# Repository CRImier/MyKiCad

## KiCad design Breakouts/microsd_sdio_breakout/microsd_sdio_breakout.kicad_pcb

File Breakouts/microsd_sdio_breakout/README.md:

# MicroSD SDIO breakout 

A MicroSD SDIO breakout with data-to-VCC pullups, card detect and decoupling capacitor.
Inspired by [a long-sold-out Tindie listing](https://www.tindie.com/products/gtalusan/microsdtf-breakout-with-pull-up-resistors/)

If you need to disable the CD pullup, you can use a hot air gun and shift the bottom resistor pack up by one resistor.
Pin headers are arranged in a way that this board can be plugged into a breadboard.
Signal names are silkscreened on the board's bottom layer, which is flat - all the components are on the bottom of the board for PnP optimization.
There's a 0805 footprint between card shield and card GND.

- PCB size: 23,5*23,5mm
- Layer count: 2

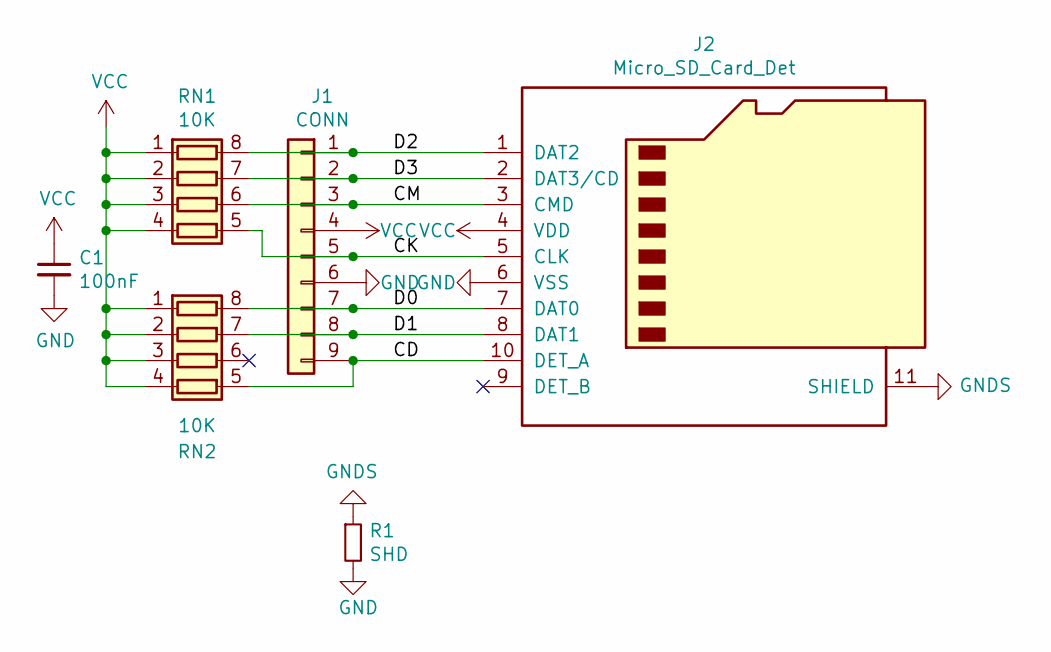
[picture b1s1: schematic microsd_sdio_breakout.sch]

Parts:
C1: 100nF; C_0805_2012Metric
J1: CONN; PinHeader_1x09_P2.54mm_Vertical
J2: Micro_SD_Card_Det; microSD-Receptacle-SelfEject
R1: SHD; R_0805_2012Metric
RN1, RN2: 10K; R_Array_Convex_4x0603

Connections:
/CD: J1.9, J2.10 (DET_A), RN2.5 (R4.2)
/CK: J1.5, J2.5 (CLK), RN1.5 (R4.2)
/CM: J1.3, J2.3 (CMD), RN1.6 (R3.2)
/D0: J1.7, J2.7 (DAT0), RN2.8 (R1.2)
/D1: J1.8, J2.8 (DAT1), RN2.7 (R2.2)
/D2: J1.1, J2.1 (DAT2), RN1.8 (R1.2)
/D3: J1.2, J2.2 (DAT3/CD), RN1.7 (R2.2)
GND: C1.2, J1.6, J2.6 (VSS), R1.2
GNDS: J2.11 (SHIELD), R1.1
VCC: C1.1, J1.4, J2.4 (VDD), RN1.1 (R1.1), RN1.2 (R2.1), RN1.3 (R3.1), RN1.4 (R4.1), RN2.1 (R1.1), RN2.2 (R2.1), RN2.3 (R3.1), RN2.4 (R4.1)

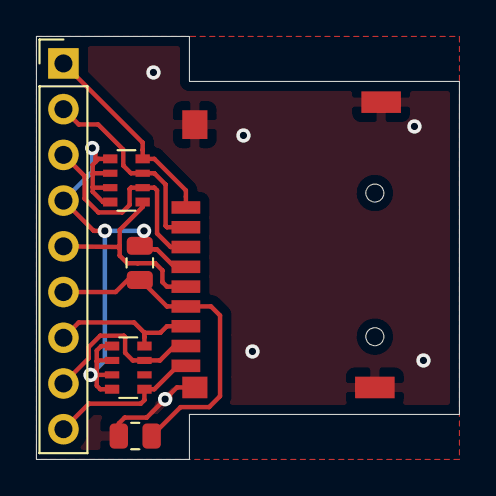
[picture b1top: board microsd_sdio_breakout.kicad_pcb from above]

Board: 2 copper layers, 23.5 x 23.5 mm, 6 parts (0 on the bottom side), 10 nets.

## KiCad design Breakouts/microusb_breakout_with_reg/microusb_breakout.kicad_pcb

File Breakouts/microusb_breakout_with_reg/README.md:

# Simple MicroUSB breakout

This is a MicroUSB connector breakout that also includes a 3.3V regulator. The 5V pin is available on the pin header,
and 3.3V is available on the bottom of the board. Pins are not marked on the bottom of the board.

- PCB size: 8mm*11mm
- Layer count: 2

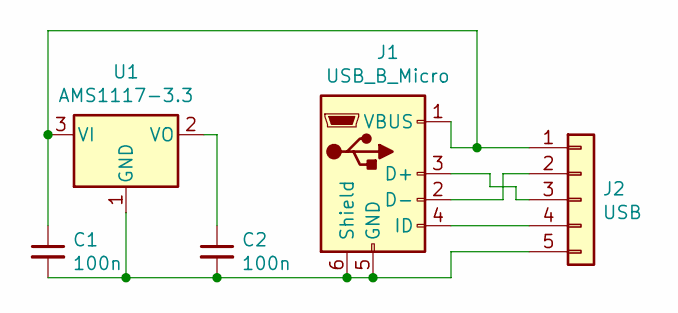
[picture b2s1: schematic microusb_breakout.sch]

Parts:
C1, C2: 100n; C_0805_2012Metric
J1: USB_B_Micro; MICROUSB_REINFORCED
J2: USB; PinHeader_1x05_P2.00mm_Vertical
U1: AMS1117-3.3; SOT-223-3_TabPin2

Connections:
unnamed: C1.1, J1.1 (VBUS), J2.1, U1.3 (VI)
unnamed: C1.2, C2.2, J1.5 (GND), J1.6 (Shield), J2.5, U1.1 (GND)
unnamed: C2.1, U1.2 (VO)
unnamed: J1.2 (D-), J2.2
unnamed: J1.3 (D+), J2.3
unnamed: J1.4 (ID), J2.4

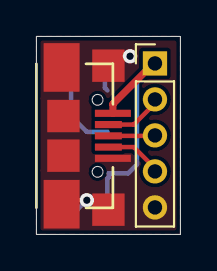
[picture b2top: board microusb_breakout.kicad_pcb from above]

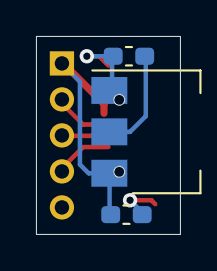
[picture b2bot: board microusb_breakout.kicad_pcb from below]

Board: 2 copper layers, 8.0 x 11.0 mm, 5 parts (3 on the bottom side), 6 nets.

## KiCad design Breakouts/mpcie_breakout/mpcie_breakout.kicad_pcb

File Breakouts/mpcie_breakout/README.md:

# mPCI-E breakout board

This is a mPCI-e (miniPCI-express) receptacle breakout that aims to be as fully-featured as possible while keeping the price low.
It allows you to work with a wide range of mPCIe devices - from consumer-oriented mPCIe cards
(i.e. WiFi, BT, GSM and GPS mPCI-e cards and mSATA drives)
to other cards for hobbyist and specialist use
(mPCI-E breakouts for MCUs, RF-oriented mPCI-E cards and other mPCIe cards of all kinds)

This board has a MicroUSB socket and a SIM socket, as well as a footprint to add 1117-SOT223 compatible linear regulators
from VBUS to 3.3V and 1.5V power lines. All 1.5V pins can be disconnected from the 1.5V power bus in case your card uses these
pins for some other purpose

Keep in mind that PCI-E signals aren't impedance-matched to the PCB, in fact,
the trace thickness and clearances for the diffpairs was not chosen with any specific purpose in mind.

The board is intended to be self-documenting - the signal numbers are silkscreened on the board,
and the PCI-E pinout is written on the bottom of the board. There's also a mSATA pin mapping cheatsheet.

## Changes in v3:

- Moved to Kicad 5
- PCIe diffpairs made a tad better

## Changes in v2:

- SIM slot pinout has been fixed
- Added 1117 footprint regulators for 3.3V and 1.5V lines
- Made standoff holes more compatible with popular solderable standoffs
- Made mounting holes M3 and M4 instead of random diameters, spaced them apart in a way that made more sense
- Changed 0R resistors to 0603 - allowing easier handsoldering of the bottom side (bottom side has optional components for 1.5V and 3.3V regulators)
- Made mPCIe socket alignment pin holes smaller so that they can actually help with alignment
- Made a cutout for USB socket "lips" to allow for easier panelization
- Added fiducials
- Replaced the capacitor footprint with the one used in stock libraries

- Signal names are silkscreened on the board, top and bottom layers.
- This repository also includes files for manufacturing a 3x2 panel.
- I recommend a stencil for assembling this board.

- Software: Kicad 6
- Version: 3
- PCB size: 73*42mm
- Layer count: 2
- Recommended thickness: non-thin

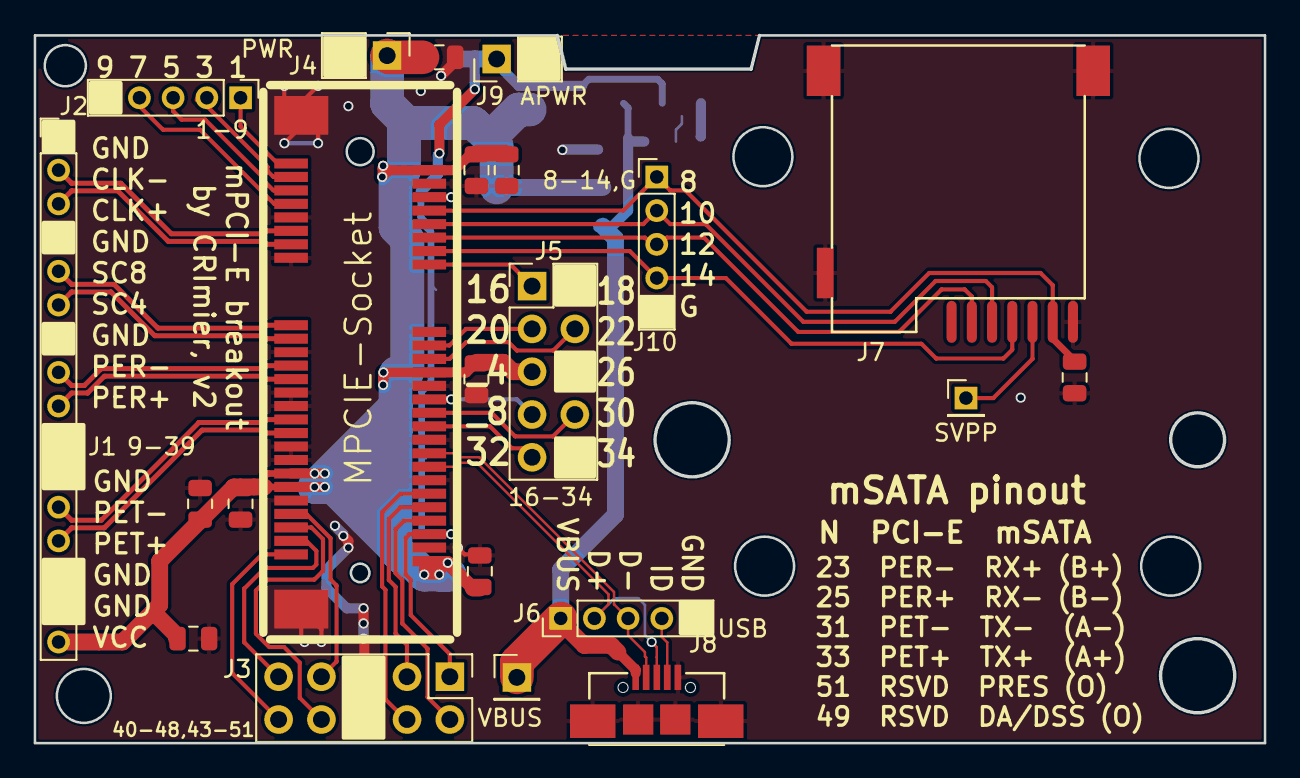
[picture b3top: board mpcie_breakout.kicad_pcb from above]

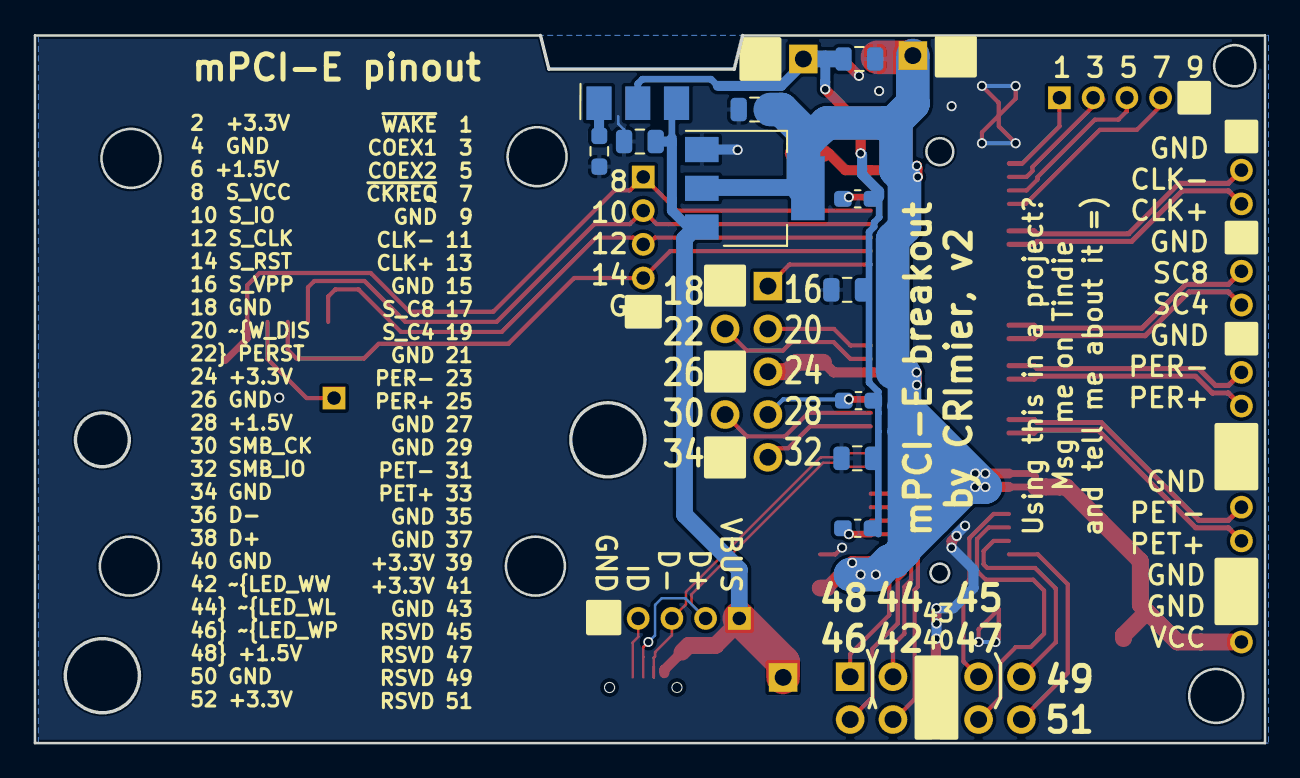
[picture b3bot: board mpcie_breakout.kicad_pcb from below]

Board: 2 copper layers, 73.0 x 42.0 mm, 33 parts (11 on the bottom side), 40 nets.

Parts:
C1, C2, C3, C4, C5, C6, C7, C8, C9, C10, C11, C12, C13, C14: 100nF; C_0805_2012Metric
J1: 9-39; Pin_Header_Straight_1x16_Pitch2.00mm
J2: 1-9; Pin_Header_Straight_1x05_Pitch2.00mm
J3: 40-48,43-51; Pin_Header_Straight_2x05_Pitch2.54mm
J4: PWR; Pin_Header_Straight_1x02_Pitch2.54mm
J5: 16-34; Pin_Header_Straight_2x05_Pitch2.54mm
J6: USB; Pin_Header_Straight_1x05_Pitch2.00mm
J7: SIM_Card; MICROSIM_6P_SMD_HOLDER
J8: USB_OTG; MICROUSB_SIMPLE
J9: APWR; Pin_Header_Straight_1x02_Pitch2.54mm
J10: 8-14,G; Pin_Header_Straight_1x05_Pitch2.00mm
R1, R2, R3: 0; R_0603_1608Metric_Pad1.05x0.95mm_HandSolder
R4: 0/ADJ; R_0603_1608Metric_Pad0.98x0.95mm_HandSolder
TP1: SVPP; Pin_Header_Straight_1x01_Pitch2.00mm
TP2: VBUS; Pin_Header_Straight_1x01_Pitch2.54mm
U1: MPCIE-Socket; mpcie-socket
U2: AP1117-33; SOT-223-3_TabPin2
U3: AP1117-15; SOT-223-3_TabPin2

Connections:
+1V5: C10.1, C11.1, C12.1, J9.1, R1.2, R2.2, R3.2, U3.2
/CLK+: J1.3, U1.13
/CLK-: J1.2, U1.11
/D+: J6.2, J8.3, U1.38
/D-: J6.3, J8.2, U1.36
/PER+: J1.9, U1.25
/PER-: J1.8, U1.23
/PET0+: J1.13, U1.33
/PET0-: J1.12, U1.31
/SIM_CLK: J7.C3, J10.3, U1.12
/SIM_IO: J7.C7, J10.2, U1.10
/SIM_RST: J7.C2, J10.4, U1.14
/SIM_VCC: C9.1, J7.C1, J10.1, U1.8
/SIM_VPP: J7.C6, TP1.1
/SMH+: J1.6, U1.19
/SMH-: J1.5, U1.17
GND: C1.2, C2.2, C3.2, C4.2, C5.2, C6.2, C7.2, C8.2, C9.2, C10.2, C11.2, C12.2, C13.2, C14.2, J1.1, J1.4, J1.7, J1.10, J1.11, J1.14, J1.15, J2.5, J3.5, J3.6, J4.2, J5.2, J5.6, J5.10, J6.5, J7.8, J7.C5, J8.5, J8.6, J9.2, J10.5, R4.2, U1.4, U1.9, U1.15, U1.18, U1.21, U1.26, U1.27, U1.29, U1.34, U1.35, U1.37, U1.40, U1.43, U1.50, U2.1
unnamed: J2.1, U1.1
unnamed: J2.2, U1.3
unnamed: J2.3, U1.5
unnamed: J2.4, U1.7
unnamed: J3.1, R3.1, U1.48
unnamed: J3.2, U1.46
unnamed: J3.3, U1.44
unnamed: J3.4, U1.42
unnamed: J3.7, U1.45
unnamed: J3.8, U1.47
unnamed: J3.9, U1.49
unnamed: J3.10, U1.51
unnamed: J5.1, U1.16
unnamed: J5.3, U1.20
unnamed: J5.4, U1.22
unnamed: J5.7, R2.1, U1.28
unnamed: J5.8, U1.30
unnamed: J5.9, U1.32
unnamed: J6.4, J8.4
unnamed: R1.1, U1.6
unnamed: R4.1, U3.1
VBUS: C14.1, J6.1, J8.1, TP2.1, U2.3, U3.3
VCC: C1.1, C2.1, C3.1, C4.1, C5.1, C6.1, C7.1, C8.1, C13.1, J1.16, J4.1, J5.5, U1.2, U1.24, U1.39, U1.41, U1.52, U2.2

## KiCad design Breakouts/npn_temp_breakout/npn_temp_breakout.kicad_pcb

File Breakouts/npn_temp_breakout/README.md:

# PNP transistor temperature sensing breakout

This is a board I plan to use with MAX6636 for temperature sensing. It's a PNP (3906)
transistor breakout with two of the transistor's legs joined together. The MAX6636 datasheet
is weird in that it calls for a 3904 transistor in its recommended parts section, which is NPN,
but the schematic symbols and the datasheet mentions PNP transistors. I didn't check if this
breakout would be suitable for 3904, this is all yet to be tested properly.

The pad with silkscreen square around it is the "+" pad for PNP transistor, if I'm not mistaken.

There's a copper via going from the bottom layer to the top layer, to where the transistor is:
my intention is that it ought to make thermal transfer better. I'm not sure if this is actually
the case. Oh, also, there's an exposed copper polygon on the bottom, but it'll break if you
reload the netlist by i.e. F8, so you'll need to re-add a trace from PNP's pin 3 to re-fill it.
Delete the trace after re-filling so that it doesn't cause interference.

I'd recommend connecting these boards to a main board with something like a twisted pair (from i.e. an
Ethernet cable)

This board is untested and there's no guarantees of fitness.

- PCB size: 5.6x4mm
- Layer count: 2

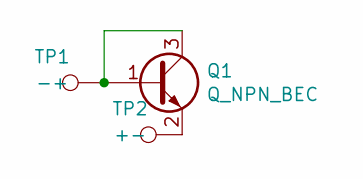
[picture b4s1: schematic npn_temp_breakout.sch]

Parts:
Q1: Q_NPN_BEC; SOT-23
TP1: -+; TestPoint_Pad_1.5x1.5mm
TP2: +-; TestPoint_Pad_1.5x1.5mm

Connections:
unnamed: Q1.1 (B), Q1.3 (C), TP1.1
unnamed: Q1.2 (E), TP2.1

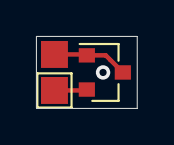
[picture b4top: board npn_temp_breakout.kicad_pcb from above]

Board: 2 copper layers, 5.6 x 4.0 mm, 3 parts (0 on the bottom side), 2 nets.

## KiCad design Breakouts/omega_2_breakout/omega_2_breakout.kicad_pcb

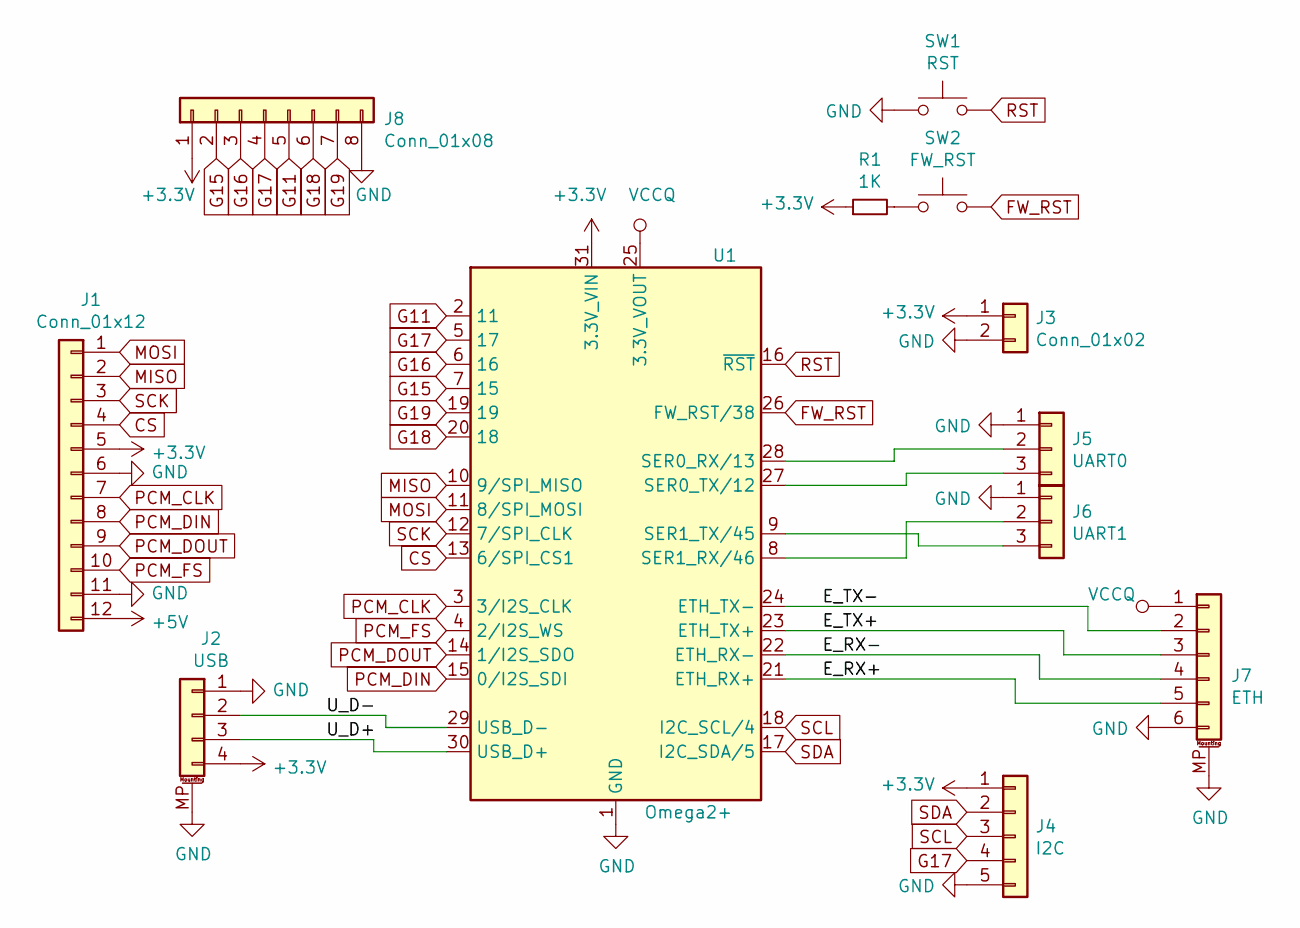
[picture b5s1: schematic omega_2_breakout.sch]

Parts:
J1: Conn_01x12; PinSocket_1x12_P2.54mm_Horizontal
J2: USB; JST_SH_SM04B-SRSS-TB_1x04-1MP_P1.00mm_Horizontal
J3: Conn_01x02; PinHeader_1x02_P2.54mm_Vertical
J4: I2C; PinSocket_1x05_P2.54mm_Horizontal
J5: UART0; PinHeader_1x03_P2.54mm_Vertical
J6: UART1; PinHeader_1x03_P2.54mm_Vertical
J7: ETH; JST_SH_SM06B-SRSS-TB_1x06-1MP_P1.00mm_Horizontal
J8: Conn_01x08; PinHeader_1x08_P2.54mm_Horizontal
R1: 1K; R_0805_2012Metric
SW1: RST; SW_SPST_EVQPE1
SW2: FW_RST; SW_SPST_EVQPE1
U1: Omega2+; Onion_Omega2+

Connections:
+3V3: J1.5, J2.4, J3.1, J4.1, J8.1, R1.1, U1.31 (3.3V_VIN)
/E_RX+: J7.5, U1.21 (ETH_RX+)
/E_RX-: J7.4, U1.22 (ETH_RX-)
/E_TX+: J7.3, U1.23 (ETH_TX+)
/E_TX-: J7.2, U1.24 (ETH_TX-)
/U_D+: J2.3, U1.30 (USB_D+)
/U_D-: J2.2, U1.29 (USB_D-)
CS: J1.4, U1.13 (6/SPI_CS1)
FW_RST: SW2.2, U1.26 (FW_RST/38)
G11: J8.5, U1.2 (11)
G15: J8.2, U1.7 (15)
G16: J8.3, U1.6 (16)
G17: J4.4, J8.4, U1.5 (17)
G18: J8.6, U1.20 (18)
G19: J8.7, U1.19
GND: J1.6, J1.11, J2.1, J2.MP (MountPin), J3.2, J4.5, J5.1, J6.1, J7.6, J7.MP (MountPin), J8.8, SW1.1, U1.1 (GND), U1.32 (GND)
MISO: J1.2, U1.10 (9/SPI_MISO)
MOSI: J1.1, U1.11 (8/SPI_MOSI)
unnamed: J5.2, U1.28 (SER0_RX/13)
unnamed: J5.3, U1.27 (SER0_TX/12)
unnamed: J6.2, U1.8 (SER1_RX/46)
unnamed: J6.3, U1.9 (SER1_TX/45)
unnamed: R1.2, SW2.1
PCM_CLK: J1.7, U1.3 (3/I2S_CLK)
PCM_DIN: J1.8, U1.15 (0/I2S_SDI)
PCM_DOUT: J1.9, U1.14 (1/I2S_SDO)
PCM_FS: J1.10, U1.4 (2/I2S_WS)
RST: SW1.2, U1.16 (~RST)
SCK: J1.3, U1.12 (7/SPI_CLK)
SCL: J4.3, U1.18 (I2C_SCL/4)
SDA: J4.2, U1.17 (I2C_SDA/5)
VCCQ: J7.1, U1.25 (3.3V_VOUT)

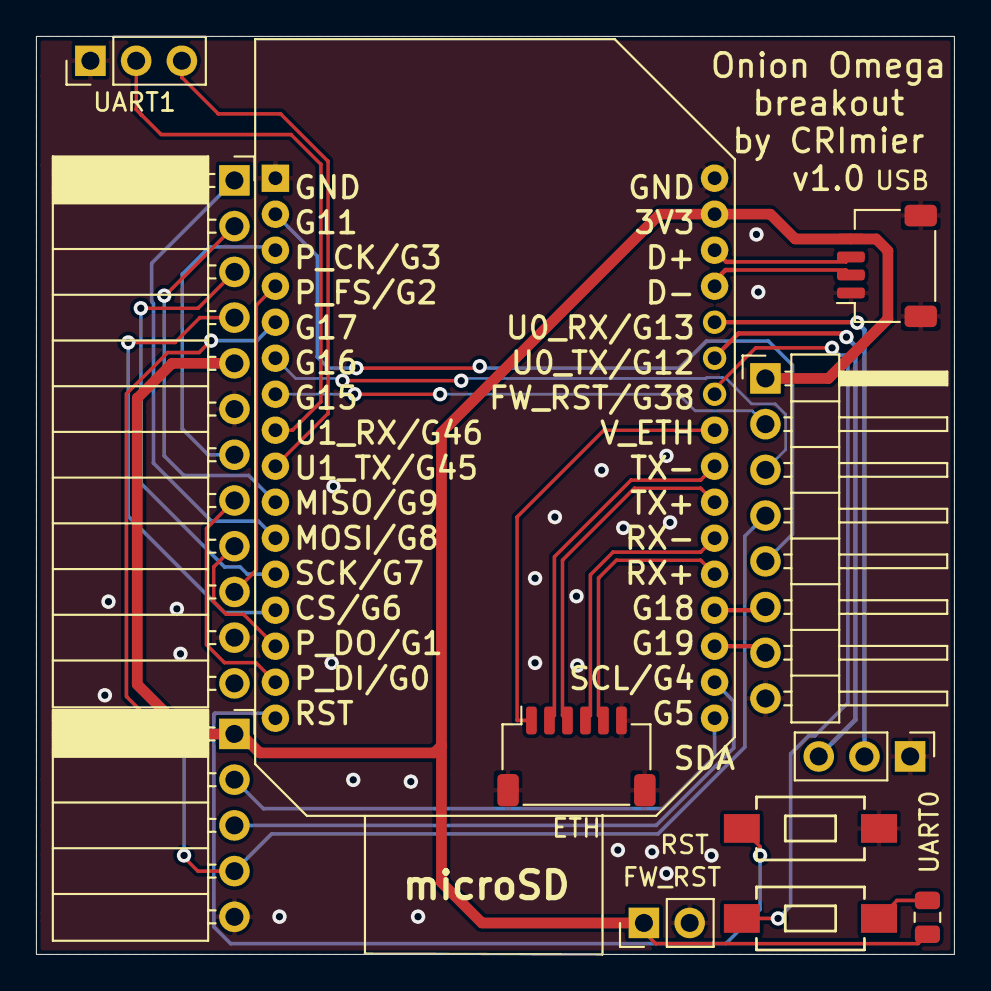
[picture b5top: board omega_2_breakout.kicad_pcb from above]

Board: 2 copper layers, 51.0 x 51.0 mm, 12 parts (0 on the bottom side), 32 nets.

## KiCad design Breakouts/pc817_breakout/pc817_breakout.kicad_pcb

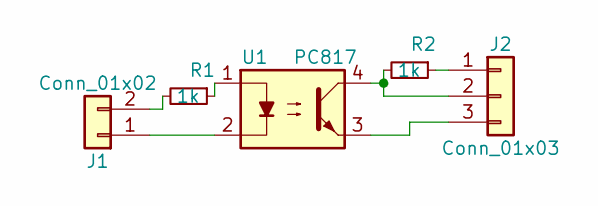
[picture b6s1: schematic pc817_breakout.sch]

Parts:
J1: Conn_01x02; Pin_Header_Straight_1x02_Pitch2.54mm
J2: Conn_01x03; Pin_Header_Straight_1x03_Pitch2.54mm
R1, R2: 1k; R_0805_HandSoldering
U1: PC817; DIP-4_W7.62mm

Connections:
unnamed: J1.1, U1.2
unnamed: J1.2, R1.2
unnamed: J2.1, R2.1
unnamed: J2.2, R2.2, U1.4
unnamed: J2.3, U1.3
unnamed: R1.1, U1.1

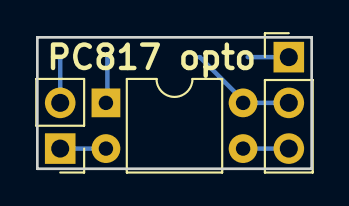
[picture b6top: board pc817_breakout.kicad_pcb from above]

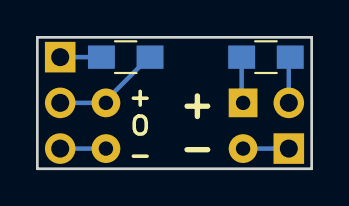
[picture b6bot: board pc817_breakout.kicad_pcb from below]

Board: 2 copper layers, 15.2 x 7.3 mm, 5 parts (2 on the bottom side), 6 nets.
